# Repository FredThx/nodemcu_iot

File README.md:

# nodemcu_iot
LUA programs for nodemcu iot devices and MQTT messages.

## Usage :

Modify the params.lua file.
Copy all files in the nodemcu device.
restart the device

## Examples :

all examples are used in my homes

## Tutorials :

http://ouiaremakers.com/les-croquettes-du-chat-en-iot/

http://ouiaremakers.com/mes-refrigerateur-congelateur-en-mode-connecte/

## devices

- 433 switch
- BMP085 (pressure, temperature)
- DHT (temperature, humidity)
- ds1820b
- flowmeter
- HC_SR04
- LCD1602
- LPS35HW
- paj7620
- MaxSonar
- mcp3008
- mcp3201
- mcp9804
- motor with L298B
- rotary sensor
- servo motor
- stepper
- tft_24
- vl6180
- D6F-V (OMRON air flow sensor)

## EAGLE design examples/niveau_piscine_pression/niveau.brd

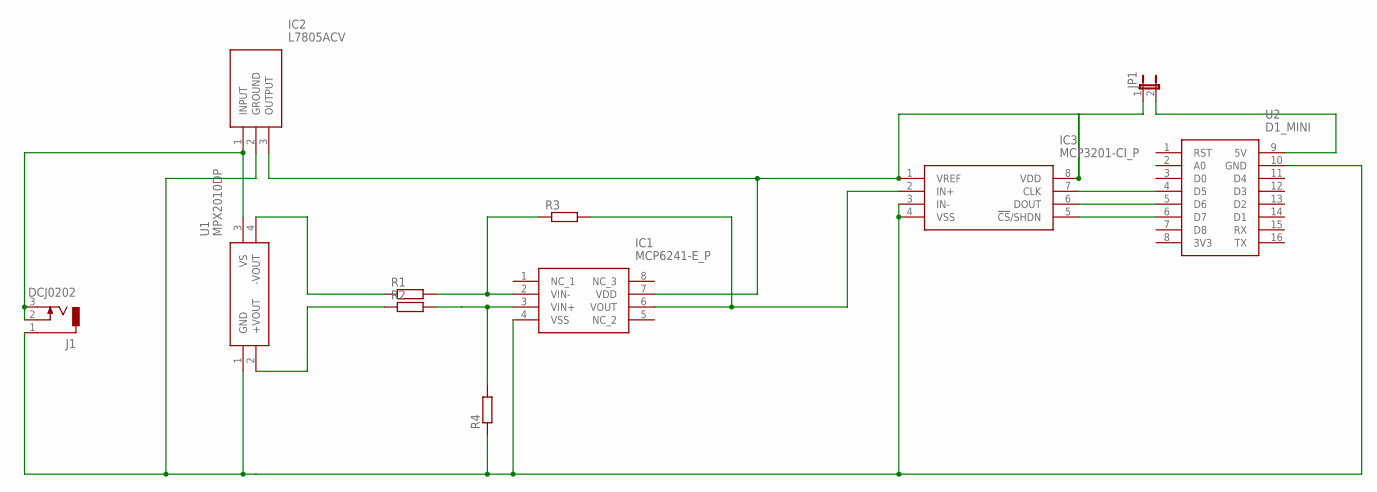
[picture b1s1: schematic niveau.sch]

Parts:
IC1: MCP6241-E_P; DIP781W56P254L950H533Q8N
IC2: L7805ACV; TO270P460X1020X2008-3P
IC3: MCP3201-CI_P; DIP781W56P254L950H533Q8N
J1: DCJ0202
JP1: JP1E; JP1
R1, R2, R3, R4: R-EU_0204/2V; 0204V
U1: MPX2010DP; CASE-344C-01-ISSUE-B
U2: D1_MINI; D1-MINI

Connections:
unnamed: R1.1, U1.4 (-VOUT)
unnamed: R2.1, U1.2 (+VOUT)
unnamed 2: IC1.4 (VSS), IC2.2 (GROUND), IC3.3 (IN-), IC3.4 (VSS), J1.1, R4.1, U1.1 (GND), U2.10 (GND); also elsewhere on the board
unnamed 3: IC2.1 (INPUT), J1.2, J1.3, U1.3 (VS); also elsewhere on the board
unnamed: IC1.6 (VOUT), IC3.2 (IN+), R3.2
unnamed: IC1.7 (VDD), IC2.3 (OUTPUT), IC3.1 (VREF), IC3.8 (VDD), JP1.1
unnamed: IC1.2 (VIN-), R1.2, R3.1
unnamed: JP1.2, U2.9 (5V)
unnamed: IC3.7 (CLK), U2.4 (D5)
unnamed: IC3.6 (DOUT), U2.5 (D6)
unnamed: IC3.5 (!CS!/SHDN), U2.6 (D7)
unnamed: IC1.3 (VIN+), R2.2, R4.2

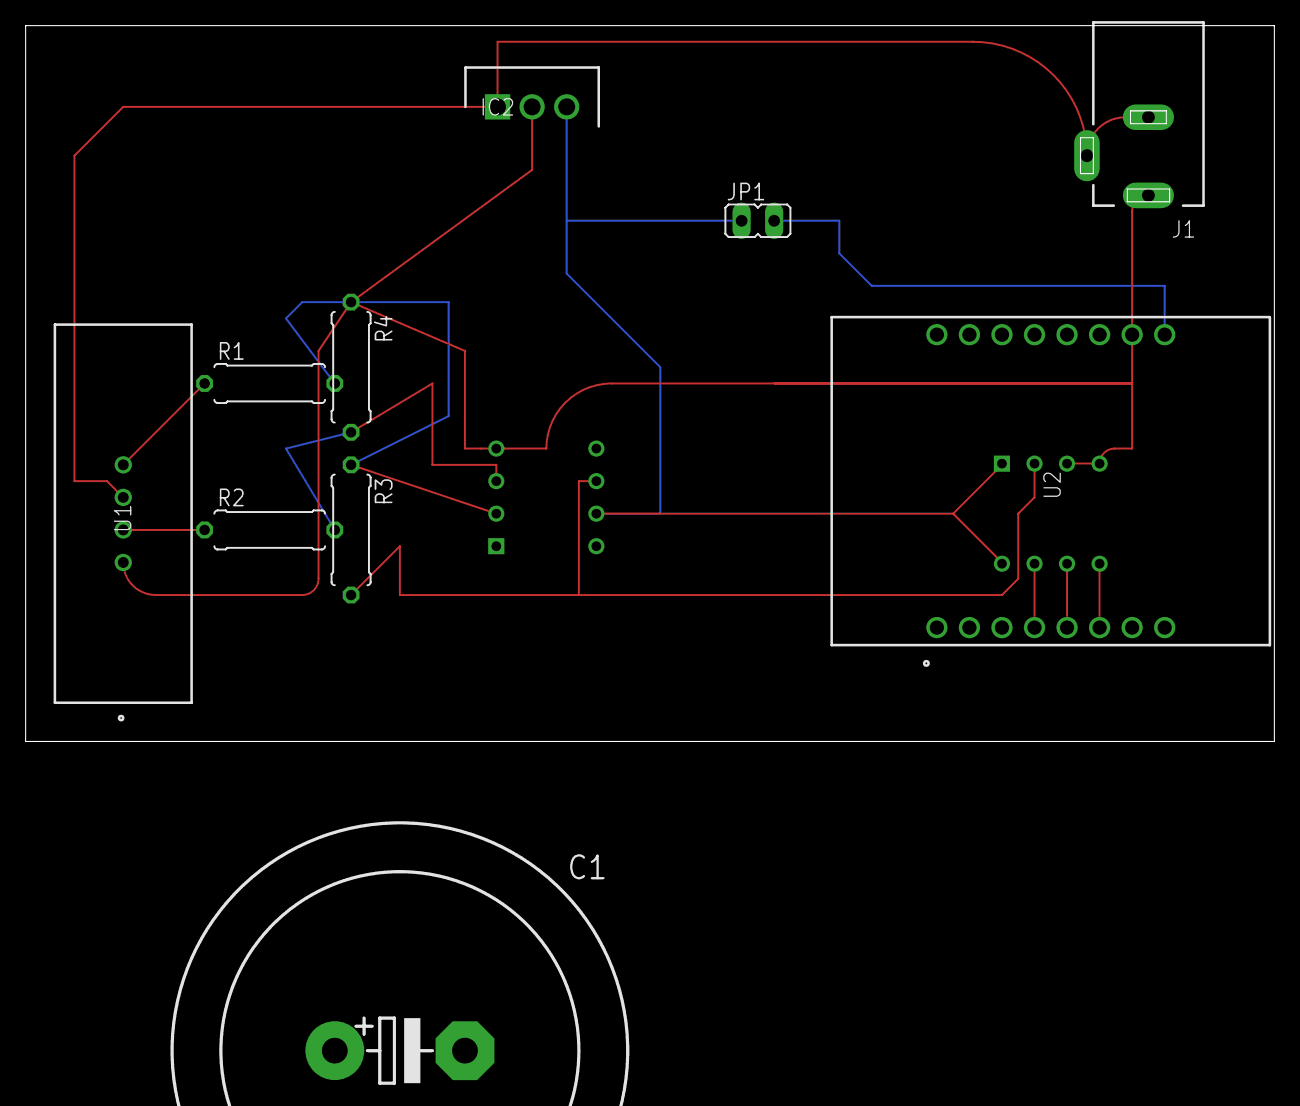
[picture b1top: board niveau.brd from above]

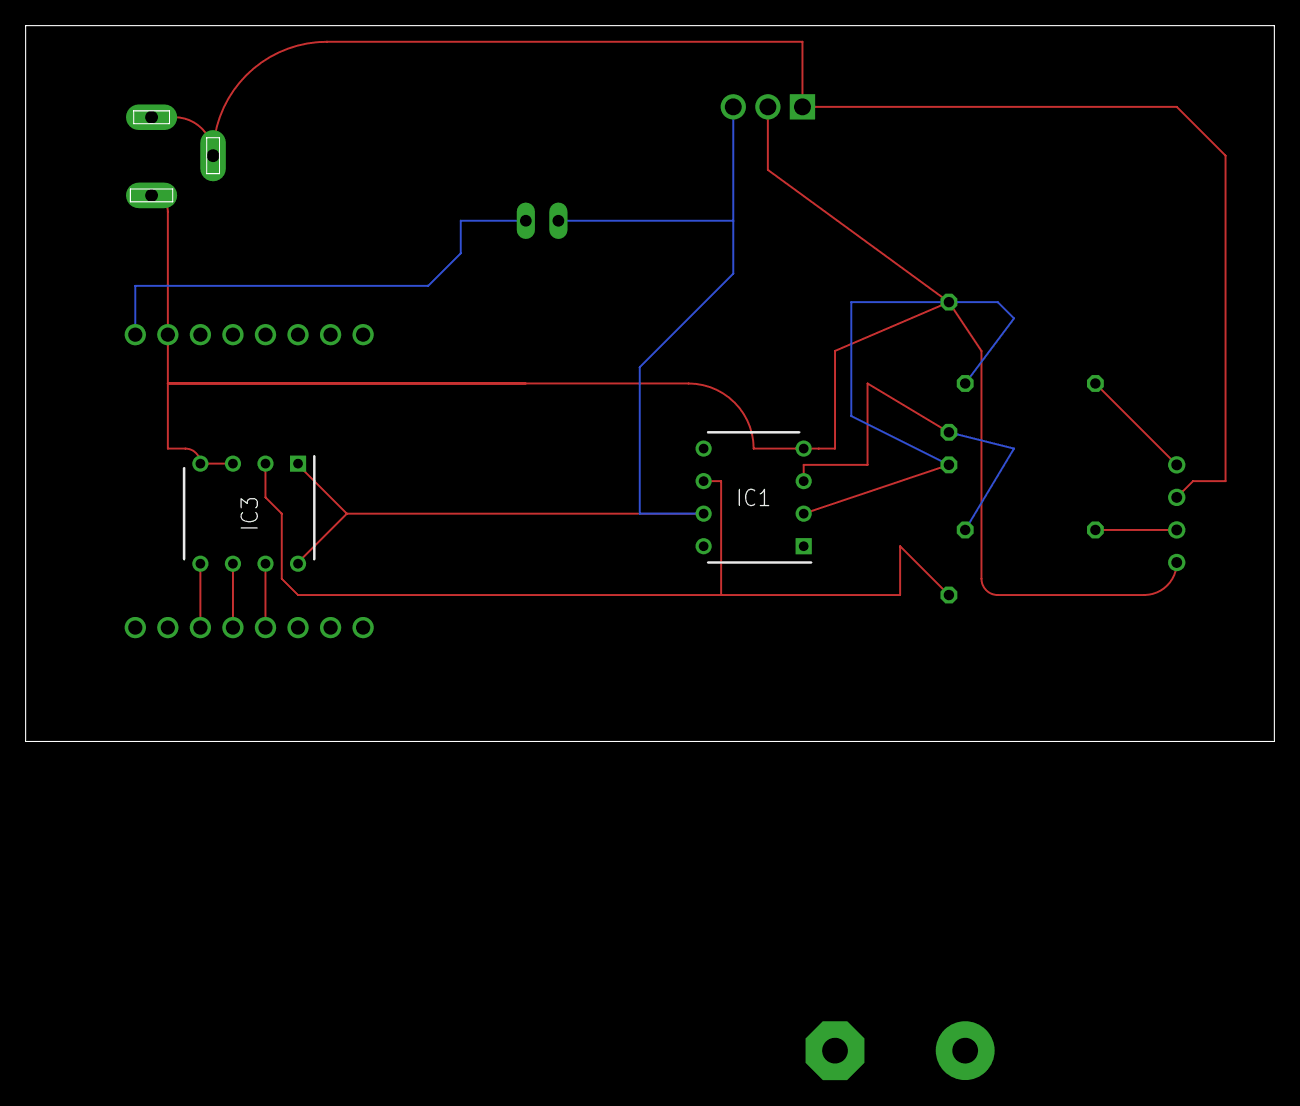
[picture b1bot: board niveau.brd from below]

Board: 2 copper layers, 97.5 x 55.9 mm, 12 parts (2 on the bottom side), 12 nets.

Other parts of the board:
C1: 1000µF; EB35D

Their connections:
unnamed 2: C1.-; also elsewhere on the board
unnamed 3: C1.+; also elsewhere on the board

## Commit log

2016-05-16 test
2016-05-22 Add mcp3008 support
    Add mcp3008 for analogue read.
    And an example (exterieur)
2016-06-12 juin update
    correct bugs about ds1820 (prevent out of memory crash)
    maj croquette example
2016-06-18 Tuto croquettes
    Update for http://ouiaremakers.com/ tuto
2016-06-24 Update croquettes
    resolve bug on node-red flow
2016-07-02 Add Ballon example + add divisor option for triggers
2016-07-02 mod README
2016-11-20 Updates
    - Memory optimizations
    - new examples
2017-02-26 Updates and new usages
    Add new devices
    - servo
    - mpu6050
    Add new examples
    - VMC
    - Porte garage
2017-04-16 Update of april
2017-07-09 Update params.lua
    Simplification
2017-07-16 juin 2017 update
2017-08-01 Juillet 2017
    Add rotary
    Add stepper
    Add examples
2018-02-10 fev 2017
    Add new devices :
    - Ultrasonic sensor HC-SR04
    - stepper motors
    Add new examples
2018-03-23 PIERRON_iot add
    add example PIERRON
    + add MCP3201 device
    + print_log : disable print if needed
    + disable delay after sending mqtt message
2018-03-25 Add vibreurs to croquettes
2018-03-25 dimanche 25 mars 2018
2018-03-30 DS18B20 module integration
    Utilisation du module (en C) DS1820 avec fonction callback.
2018-04-07 Rotary usage
2018-04-08 new rotary from scratch
2018-04-08 rotary from scratch
    En attendant que le module officiel fonctionne...
2018-04-08 Pascaline
2018-04-28 avril 2018
2018-04-29 New devices
    mcp9804
    vl6180x
2018-05-01 Niveau example
2018-05-01 bug message not function
2018-05-01 print bug
2018-05-01 Change timers
    use tmr.create() vs fixed numbers
2018-05-01 App table
2018-05-01 App.mqtt_....
2018-05-01 timers read et test avant connection reseau
2018-05-01 Examples adapt....
    not finished!
2018-06-13 juin 2018
2018-09-08 September 2018
    new device :led rbv
    new examples : horloge led, niveau_pression_piscine
    Ajout posibilité interpreteur LUA via MQTT (avec retour!)
2018-09-29 niveau piscine
2018-09-30 30/9/18
2018-10-01 septembre 2018
2018-10-06 sept 2018
2018-10-06 Multi buffer & pong
2018-10-06 luminosity & effects
2018-10-07 Horloge
2018-10-21 Add flowmeter device
2018-11-06 autocompile
2018-12-09 croquettes + TFT + ...
2018-12-15 userinit.lua
2018-12-16 TFT : free memory
2018-12-16 tft stable
2018-12-16 TFT : add screen saver
2019-01-02 TFT
    Ajout TFT rotation
    + boite exemple
2019-01-03 VMC_SDB
    Example : vmc_sdb (relais, luminosité, dht11)
    + deamon on_change
    + ...
2019-01-05 Boite fil pilote
2019-01-06 TFT
    Centrage des buttons
2019-01-06 fil pilote
2019-01-12 read_and_send via timer
2019-01-12 ya exemple
2019-01-20 radiateur_sdbe
2019-01-27 SONOFF Basic
2019-03-02 Add units
2019-03-24 mars 19
2019-05-05 Exterieur=> App
2019-05-05 Piscine : niveau
2019-05-05 Servo : class objects
2019-05-08 Cuve Fuel => App
2019-06-01 Cuisine : App.mesure_interval = 20000 exterieur : plus spécifique à un capteur (suite changement capteur DS1820)
2019-06-22 piscine
2019-09-29 mise à jour vmc + servo (add auto_stop)
2019-12-15 mqtt:connect sesure = False vs 0
2019-12-15 exemple etuve
2019-12-15 etuve
2019-12-25 boite TF
2019-12-29 bug dans read_and_send : do local ... end
2019-12-29 compile .. chk
2019-12-30 divers
2020-01-26 chaudiere & horloge
2020-04-03 Add id for buttons => possibilité de changer leur apparance en dynamique.
2020-04-25 LPS35HW
2021-01-23 Add DF6-V air flow sensor upgrade servo upgrade tft_24
    + exemples
2021-01-24 Add mqtt scanner
2021-01-25 Update mqtt connection-reconnection
2021-01-25 update ds18b20
2021-06-19 Salon : update u8g2 vs u8g BMP_reader : obsolète change cablage : 1 seul i2c
2021-07-14 WC_ext => App
2021-07-24 bureau
2021-09-12 App.redirectLUA : pipe
2021-09-12 Fil pilote : new 3D design
2021-11-06 HELLO
2021-11-06 thermostat bureau
2021-11-06 oups
2022-01-29 Ajout App.mqtt.on_connected
2022-01-29 wifi.sta.clearconfig()
2022-01-29 Examples SONOFF et +
2022-04-28 olfa_robot
